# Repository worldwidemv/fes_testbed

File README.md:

# Testbed for Functional Electrical Stimulation (FES) Devices

## Abstract
The FES Testbed is a specialised data acquisition system for measurements of transcutaneous electrical stimulation setups. The galvanic isolated measurement system transfers the high-resolution data of every detected
stimulation pulse via USB to a PC or Laptop. The stimulation pulse can use one of the 3 included skin replacement
models or can be forwarded to standard electrodes, allowing to record a normal FES application. Modular
postprocessing MATLAB functions round up the FES Testbed. These functions handle the data conversion, pulse
detection, gathering of statistics, data management and data visualisation. A MATLAB GUI for efficient pulse
examination completes the FES Testbed.

<p>
<a href="./Documentation/Vienna_FESWS_2019_FES_Testbed__Paper.pdf">More Information ...</a>
</p>

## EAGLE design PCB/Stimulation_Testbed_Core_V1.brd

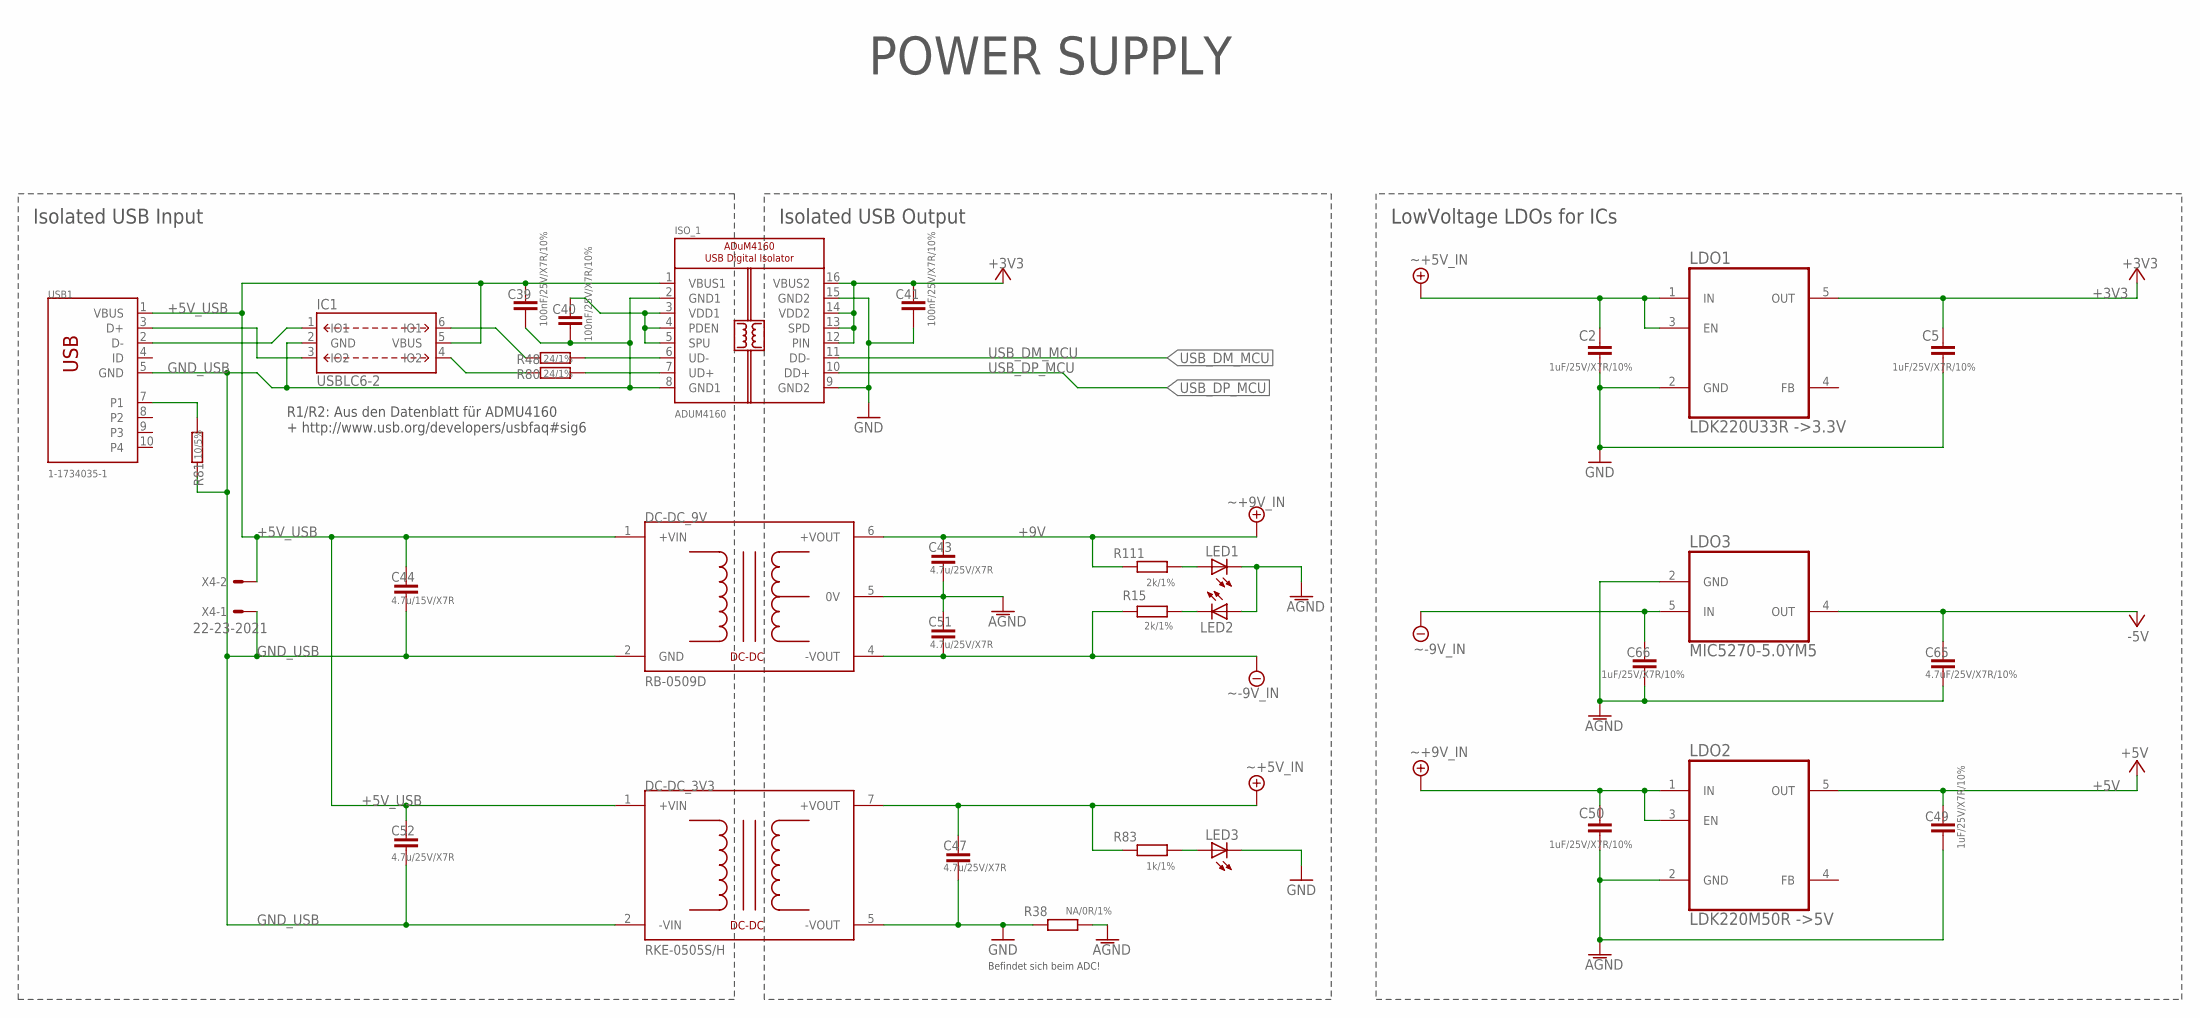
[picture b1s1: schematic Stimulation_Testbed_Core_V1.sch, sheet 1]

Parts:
C2, C5, C49, C50, C66: 1uF/25V/X7R/10%; C0603K
C39, C40, C41: 100nF/25V/X7R/10%; C0603K
C43, C47, C51, C52: 4.7u/25V/X7R; C0603
C44: 4.7u/15V/X7R; C0603
C65: 4.7uF/25V/X7R/10%; C0603K
DC-DC_3V3: RKE-0505S/H; MEJ2
DC-DC_9V: RB-0509D; NMH
IC1: USBLC6-2; SOT-23-6
ISO_1: ADUM4160; SOIC16WIDE
LDO1: LDK220U33R ->3.3V; SOT-23-5
LDO2: LDK220M50R ->5V; SOT-23-5
LDO3: MIC5270-5.0YM5; SOT-23-5
LED1, LED2, LED3: LEDCHIPLED_0603; CHIPLED_0603
R15, R111: 2k/1%; R0603
R38: NA/0R/1%; R0603
R48, R80: 24/1%; R0603
R81: 10/5%; R0603
R83: 1k/1%; R0603
USB1: 1-1734035-1; TE_1-1734035-1
X4: 22-23-2021

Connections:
+3V3: C5.1, C41.1, ISO_1.12 (PIN), ISO_1.13 (SPD), ISO_1.14 (VDD2), ISO_1.16 (VBUS2), LDO1.5 (OUT); also elsewhere on the board
+5V: C49.1, LDO2.5 (OUT); also elsewhere on the board
+5V_IN: C2.1, C47.1, DC-DC_3V3.7 (+VOUT), LDO1.1 (IN), LDO1.3 (EN), R83.1
+5V_USB: C39.1, C44.1, C52.1, DC-DC_3V3.1 (+VIN), DC-DC_9V.1 (+VIN), IC1.5 (VBUS), ISO_1.1 (VBUS1), USB1.1 (VBUS), X4.2
+9V: C43.1, C50.1, DC-DC_9V.6 (+VOUT), LDO2.1 (IN), LDO2.3 (EN), R111.1
-5V: C65.1, LDO3.4 (OUT); also elsewhere on the board
-9V: C51.2, C66.1, DC-DC_9V.4 (-VOUT), LDO3.5 (IN), R15.2
AGND: C43.2, C49.2, C50.2, C51.1, C65.2, C66.2, DC-DC_9V.5 (0V), LDO2.2 (GND), LDO3.2 (GND), LED1.C, LED2.A, R38.2; also elsewhere on the board
GND: C2.2, C5.2, C41.2, C47.2, DC-DC_3V3.5 (-VOUT), ISO_1.9 (GND2), ISO_1.15 (GND2), LDO1.2 (GND), LED3.C, R38.1; also elsewhere on the board
GND_USB: C39.2, C40.2, C44.2, C52.2, DC-DC_3V3.2 (-VIN), DC-DC_9V.2 (GND), IC1.2 (GND), ISO_1.2 (GND1), ISO_1.8 (GND1), R81.1, USB1.5 (GND), X4.1
unnamed: IC1.6 (IO1), R48.1
unnamed: C40.1, ISO_1.3 (VDD1), ISO_1.4 (PDEN), ISO_1.5 (SPU)
unnamed: ISO_1.6 (UD-), R48.2
unnamed: ISO_1.7 (UD+), R80.2
unnamed: R81.2, USB1.7 (P1)
unnamed: LED2.C, R15.1
unnamed: LED3.A, R83.2
unnamed: LED1.A, R111.2
unnamed: IC1.3 (IO2), USB1.3 (D+)
unnamed: IC1.1 (IO1), USB1.2 (D-)
unnamed: IC1.4 (IO2), R80.1
USB_DM_MCU: ISO_1.11 (DD-); also elsewhere on the board
USB_DP_MCU: ISO_1.10 (DD+); also elsewhere on the board

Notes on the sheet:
R1/R2: Aus den Datenblatt für ADMU4160 + http://www.usb.org/developers/usbfaq#sig6
Isolated USB Input
LowVoltage LDOs for ICs
Isolated USB Output
POWER SUPPLY
Befindet sich beim ADC!

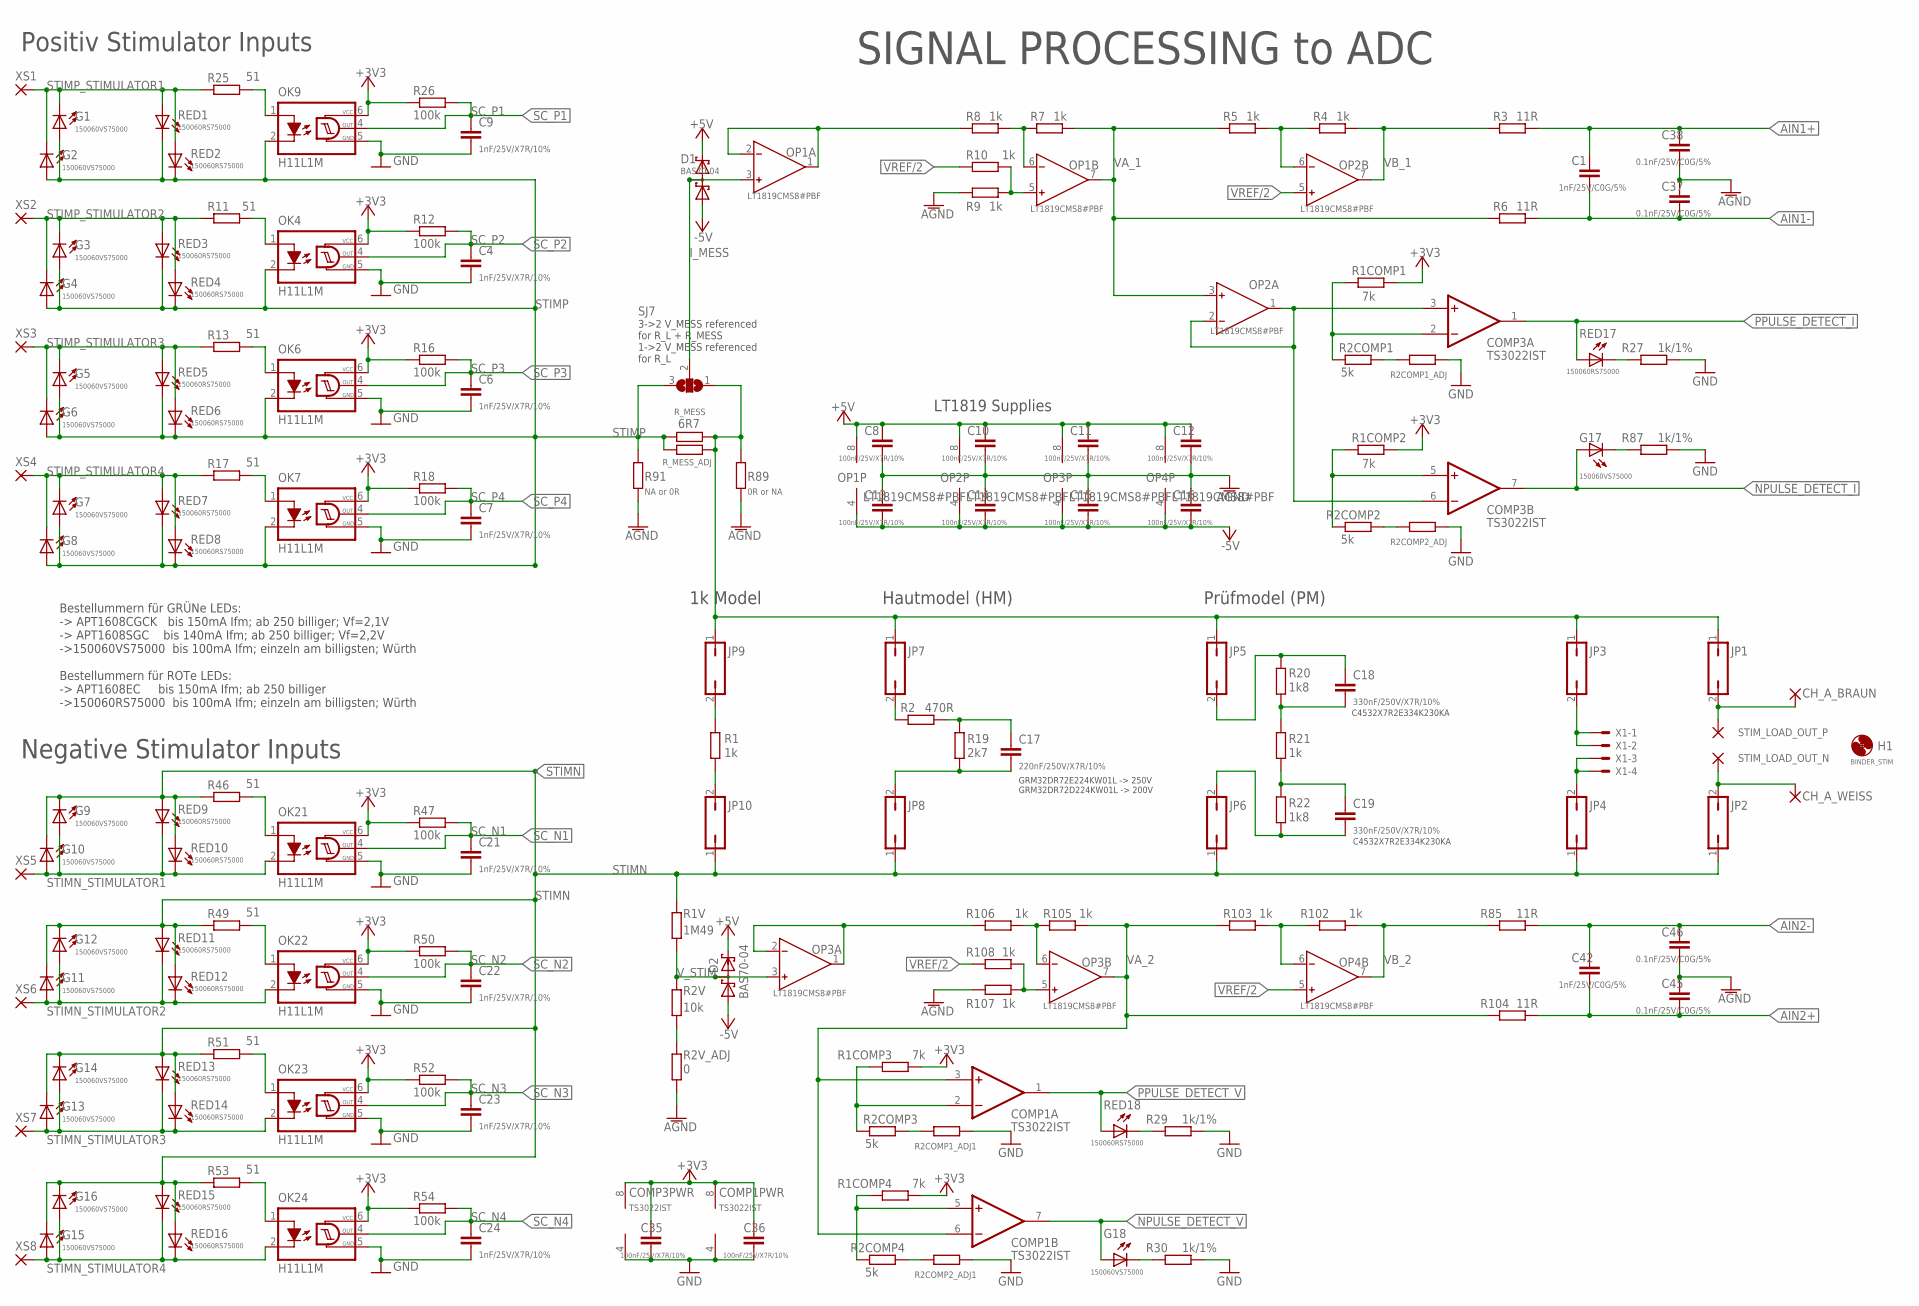
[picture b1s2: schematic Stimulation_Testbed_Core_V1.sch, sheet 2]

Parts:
C1, C42: 1nF/25V/C0G/5%; C0603K
C4, C6, C7, C9, C21, C22, C23, C24: 1nF/25V/X7R/10%; C0603
C8, C10, C11, C12, C13, C14, C15, C16, C35, C36: 100nF/25V/X7R/10%; C0603K
C17: 220nF/250V/X7R/10%; C1210
C18, C19: 330nF/250V/X7R/10%; C1812
C37, C38, C45, C46: 0.1nF/25V/C0G/5%; C0603K
CH_A_BRAUN: 1,6/0,8
CH_A_WEISS: 1,6/0,8
COMP1, COMP3: TS3022IST; MSOP8
D1, D2: BAS70-04; SOT23
G1, G2, G3, G4, G5, G6, G7, G8, G9, G10, G11, G12, G13, G14, G15, G16, G17, G18: 150060VS75000; CHIPLED_0603
H1: BINDER_STIM; 5,5-PAD
JP1, JP2, JP3, JP4, JP5, JP6, JP7, JP8, JP9, JP10: JP1Q; JP1
OK4, OK6, OK7, OK9, OK21, OK22, OK23, OK24: H11L1M; DIL06
OP1, OP2, OP3, OP4: LT1819CMS8#PBF; MSOP8
R1, R21: 1k; R1206
R1COMP1, R1COMP2, R1COMP3, R1COMP4: 7k; R0603
R1V: 1M49; R1206
R2: 470R; R1206
R2COMP1, R2COMP2, R2COMP3, R2COMP4: 5k; R0603
R2COMP1_ADJ, R2COMP1_ADJ1: R-EU_R0603; R0603
R2COMP2_ADJ, R2COMP2_ADJ1, R4, R5, R7, R8, R9, R10, R102, R103, R105, R106, R107, R108: 1k; R0603
R2V: 10k; R1206
R2V_ADJ: 0; R1206
R3, R6, R85, R104: 11R; R0603
R11, R13, R17, R25, R46, R49, R51, R53: 51; R0603
R12, R16, R18, R26, R47, R50, R52, R54: 100k; R0603
R19: 2k7; R1206
R20, R22: 1k8; R1206
R27, R29, R30, R87: 1k/1%; R0603
R89: 0R or NA; R0603
R91: NA or 0R; R0603
RED1, RED2, RED3, RED4, RED5, RED6, RED7, RED8, RED9, RED10, RED11, RED12, RED13, RED14, RED15, RED16, RED17, RED18: 150060RS75000; CHIP-LED0603
R_MESS: 6R7; R1206
R_MESS_ADJ: R-EU_R1206; R1206
SJ7: SJ2W; SJ_2
STIM_LOAD_OUT_N: 3,81/1,4
STIM_LOAD_OUT_P: 3,81/1,4
X1: 22-23-2041
XS1, XS2, XS3, XS4, XS5, XS6, XS7, XS8: WIREPAD3,81/1,4; 3,81/1,4

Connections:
2XVREF: OP3.1 (OUT), OP3.2 (IN-), R106.2
2XVREF1: OP1.1 (OUT), OP1.2 (IN-), R8.2
+3V3: C35.1, C36.1, COMP1.8 (V+), COMP3.8 (V+), OK4.6 (VCC), OK6.6 (VCC), OK7.6 (VCC), OK9.6 (VCC), OK21.6 (VCC), OK22.6 (VCC), OK23.6 (VCC), OK24.6 (VCC), R1COMP1.1, R1COMP2.1, R1COMP3.1, R1COMP4.1, R12.1, R16.1, R18.1, R26.1, R47.1, R50.1, R52.1, R54.1; also elsewhere on the board
+5V: C8.1, C10.1, C11.1, C12.1, D1.2 (C2), D2.2 (C2), OP1.8 (V+), OP2.8 (V+), OP3.8 (V+), OP4.8 (V+); also elsewhere on the board
-5V: C13.2, C14.2, C15.2, C16.2, D1.1 (A1), D2.1 (A1), OP1.4 (V-), OP2.4 (V-), OP3.4 (V-), OP4.4 (V-); also elsewhere on the board
AGND: C8.2, C10.2, C11.2, C12.2, C13.1, C14.1, C15.1, C16.1, C37.2, C38.1, C45.2, C46.1, R2V_ADJ.2, R9.2, R89.2, R91.2, R107.2; also elsewhere on the board
AIN1+: C1.2, C38.2, R3.1; also elsewhere on the board
AIN1-: C1.1, C37.1, R6.2; also elsewhere on the board
AIN2+: C42.1, C45.1, R104.2; also elsewhere on the board
AIN2-: C42.2, C46.2, R85.1; also elsewhere on the board
GND: C4.2, C6.2, C7.2, C9.2, C21.2, C22.2, C23.2, C24.2, C35.2, C36.2, COMP1.4 (V-), COMP3.4 (V-), OK4.5 (GND), OK6.5 (GND), OK7.5 (GND), OK9.5 (GND), OK21.5 (GND), OK22.5 (GND), OK23.5 (GND), OK24.5 (GND), R2COMP1_ADJ.1, R2COMP1_ADJ1.1, R2COMP2_ADJ.1, R2COMP2_ADJ1.1, R27.1, R29.1, R30.1, R87.1; also elsewhere on the board
I_MESS: D1.3 (C1A2), OP1.3 (IN+), SJ7.2
unnamed: OK4.1 (A), R11.1
unnamed: R2COMP2.2, R2COMP2_ADJ.2
unnamed: R29.2, RED18.C
unnamed: G18.C, R30.2
unnamed: COMP1.2 (-IN), R1COMP3.2, R2COMP3.1
unnamed: COMP1.5 (+IN), R1COMP4.2, R2COMP4.1
unnamed: G17.C, R87.2
unnamed: OP1.5 (IN+), R9.1, R10.1
unnamed: R2COMP1_ADJ1.2, R2COMP3.2
unnamed: R2COMP2_ADJ1.2, R2COMP4.2
unnamed: OK6.1 (A), R13.1
unnamed: OK7.1 (A), R17.1
unnamed: OK9.1 (A), R25.1
unnamed: OP1.6 (IN-), R7.2, R8.1
unnamed: OP2.6 (IN-), R4.2, R5.1
unnamed: COMP3.3 (+IN), COMP3.6 (-IN), OP2.1 (OUT), OP2.2 (IN-)
unnamed: OK21.1 (A), R46.1
unnamed: COMP3.2 (-IN), R1COMP1.2, R2COMP1.1
unnamed: CH_A_WEISS.1, JP2.2, STIM_LOAD_OUT_N.1
unnamed: OK22.1 (A), R49.1
unnamed: OK23.1 (A), R51.1
unnamed: OK24.1 (A), R53.1
unnamed: R2V.1, R2V_ADJ.1
unnamed: OP3.5 (IN+), R107.1, R108.1
unnamed: CH_A_BRAUN.1, JP1.2, STIM_LOAD_OUT_P.1
unnamed: JP3.2, X1.1, X1.2
unnamed: JP9.2, R1.1
unnamed: JP4.2, X1.3, X1.4
unnamed: JP10.2, R1.2
unnamed: JP7.2, R2.2
unnamed: OP3.6 (IN-), R105.2, R106.1
unnamed: C17.1, JP8.2, R19.2
unnamed: C19.2, R21.2, R22.1
unnamed: C19.1, JP6.2, R22.2
unnamed: C18.2, JP5.2, R20.1
unnamed: C18.1, R20.2, R21.1
unnamed: OP4.6 (IN-), R102.2, R103.1
unnamed: C17.2, R2.1, R19.1
unnamed: R27.2, RED17.C
unnamed: COMP3.5 (+IN), R1COMP2.2, R2COMP2.1
unnamed: R2COMP1.2, R2COMP1_ADJ.2
NPULSE_DETECT_I: COMP3.7 (OUT), G17.A; also elsewhere on the board
NPULSE_DETECT_V: COMP1.7 (OUT), G18.A; also elsewhere on the board
PPULSE_DETECT_I: COMP3.1 (OUT), RED17.A; also elsewhere on the board
PPULSE_DETECT_V: COMP1.1 (OUT), RED18.A; also elsewhere on the board
SC_N1: C21.1, OK21.4 (OUT), R47.2; also elsewhere on the board
SC_N2: C22.1, OK22.4 (OUT), R50.2; also elsewhere on the board
SC_N3: C23.1, OK23.4 (OUT), R52.2; also elsewhere on the board
SC_N4: C24.1, OK24.4 (OUT), R54.2; also elsewhere on the board
SC_P1: C9.1, OK9.4 (OUT), R26.2; also elsewhere on the board
SC_P2: C4.1, OK4.4 (OUT), R12.2; also elsewhere on the board
SC_P3: C6.1, OK6.4 (OUT), R16.2; also elsewhere on the board
SC_P4: C7.1, OK7.4 (OUT), R18.2; also elsewhere on the board
STIMN: G9.C, G10.C, G11.C, G12.C, G13.C, G14.C, G15.C, G16.C, JP2.1, JP4.1, JP6.1, JP8.1, JP10.1, R1V.2, R46.2, R49.2, R51.2, R53.2, RED9.A, RED10.A, RED11.A, RED12.A, RED13.A, RED14.A, RED15.A, RED16.A; also elsewhere on the board
STIMN_STIMULATOR1: G9.A, G10.A, OK21.2 (C), RED9.C, RED10.C, XS5.1
STIMN_STIMULATOR2: G11.A, G12.A, OK22.2 (C), RED11.C, RED12.C, XS6.1
STIMN_STIMULATOR3: G13.A, G14.A, OK23.2 (C), RED13.C, RED14.C, XS7.1
STIMN_STIMULATOR4: G15.A, G16.A, OK24.2 (C), RED15.C, RED16.C, XS8.1
STIMP: G1.A, G2.A, G3.A, G4.A, G5.A, G6.A, G7.A, G8.A, OK4.2 (C), OK6.2 (C), OK7.2 (C), OK9.2 (C), R91.1, RED1.C, RED2.C, RED3.C, RED4.C, RED5.C, RED6.C, RED7.C, RED8.C, R_MESS.2, R_MESS_ADJ.1, SJ7.3; also elsewhere on the board
STIMP_MODEL: JP1.1, JP3.1, JP5.1, JP7.1, JP9.1, R89.1, R_MESS.1, R_MESS_ADJ.2, SJ7.1
STIMP_STIMULATOR1: G1.C, G2.C, R25.2, RED1.A, RED2.A, XS1.1
STIMP_STIMULATOR2: G3.C, G4.C, R11.2, RED3.A, RED4.A, XS2.1
STIMP_STIMULATOR3: G5.C, G6.C, R13.2, RED5.A, RED6.A, XS3.1
STIMP_STIMULATOR4: G7.C, G8.C, R17.2, RED7.A, RED8.A, XS4.1
VA_1: OP1.7 (OUT), OP2.3 (IN+), R5.2, R6.1, R7.1
VA_2: COMP1.3 (+IN), COMP1.6 (-IN), OP3.7 (OUT), R103.2, R104.1, R105.1
VB_1: OP2.7 (OUT), R3.2, R4.1
VB_2: OP4.7 (OUT), R85.2, R102.1
VREF/2: OP2.5 (IN+), OP4.5 (IN+), R10.2, R108.2; also elsewhere on the board
V_STIM: D2.3 (C1A2), OP3.3 (IN+), R1V.1, R2V.2

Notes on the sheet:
LT1819 Supplies
1k Model
Hautmodel (HM)
Prüfmodel (PM)
SIGNAL PROCESSING to ADC
3->2 V_MESS referenced for R_L + R_MESS 1->2 V_MESS referenced for R_L
Positiv Stimulator Inputs
Negative Stimulator Inputs
C4532X7R2E334K230KA
GRM32DR72E224KW01L -> 250V GRM32DR72D224KW01L -> 200V
Bestellummern für GRÜNe LEDs: -> APT1608CGCK bis 150mA Ifm; ab 250 billiger; Vf=2,1V -> APT1608SGC bis 140mA Ifm; ab 250 billiger; Vf=2,2V ->150060VS75000 bis 100mA Ifm; einzeln am billigsten; Würth Bestellummern für ROTe LEDs: -> APT1608EC bis 150mA Ifm; ab 250 billiger ->150060RS75000 bis 100mA I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

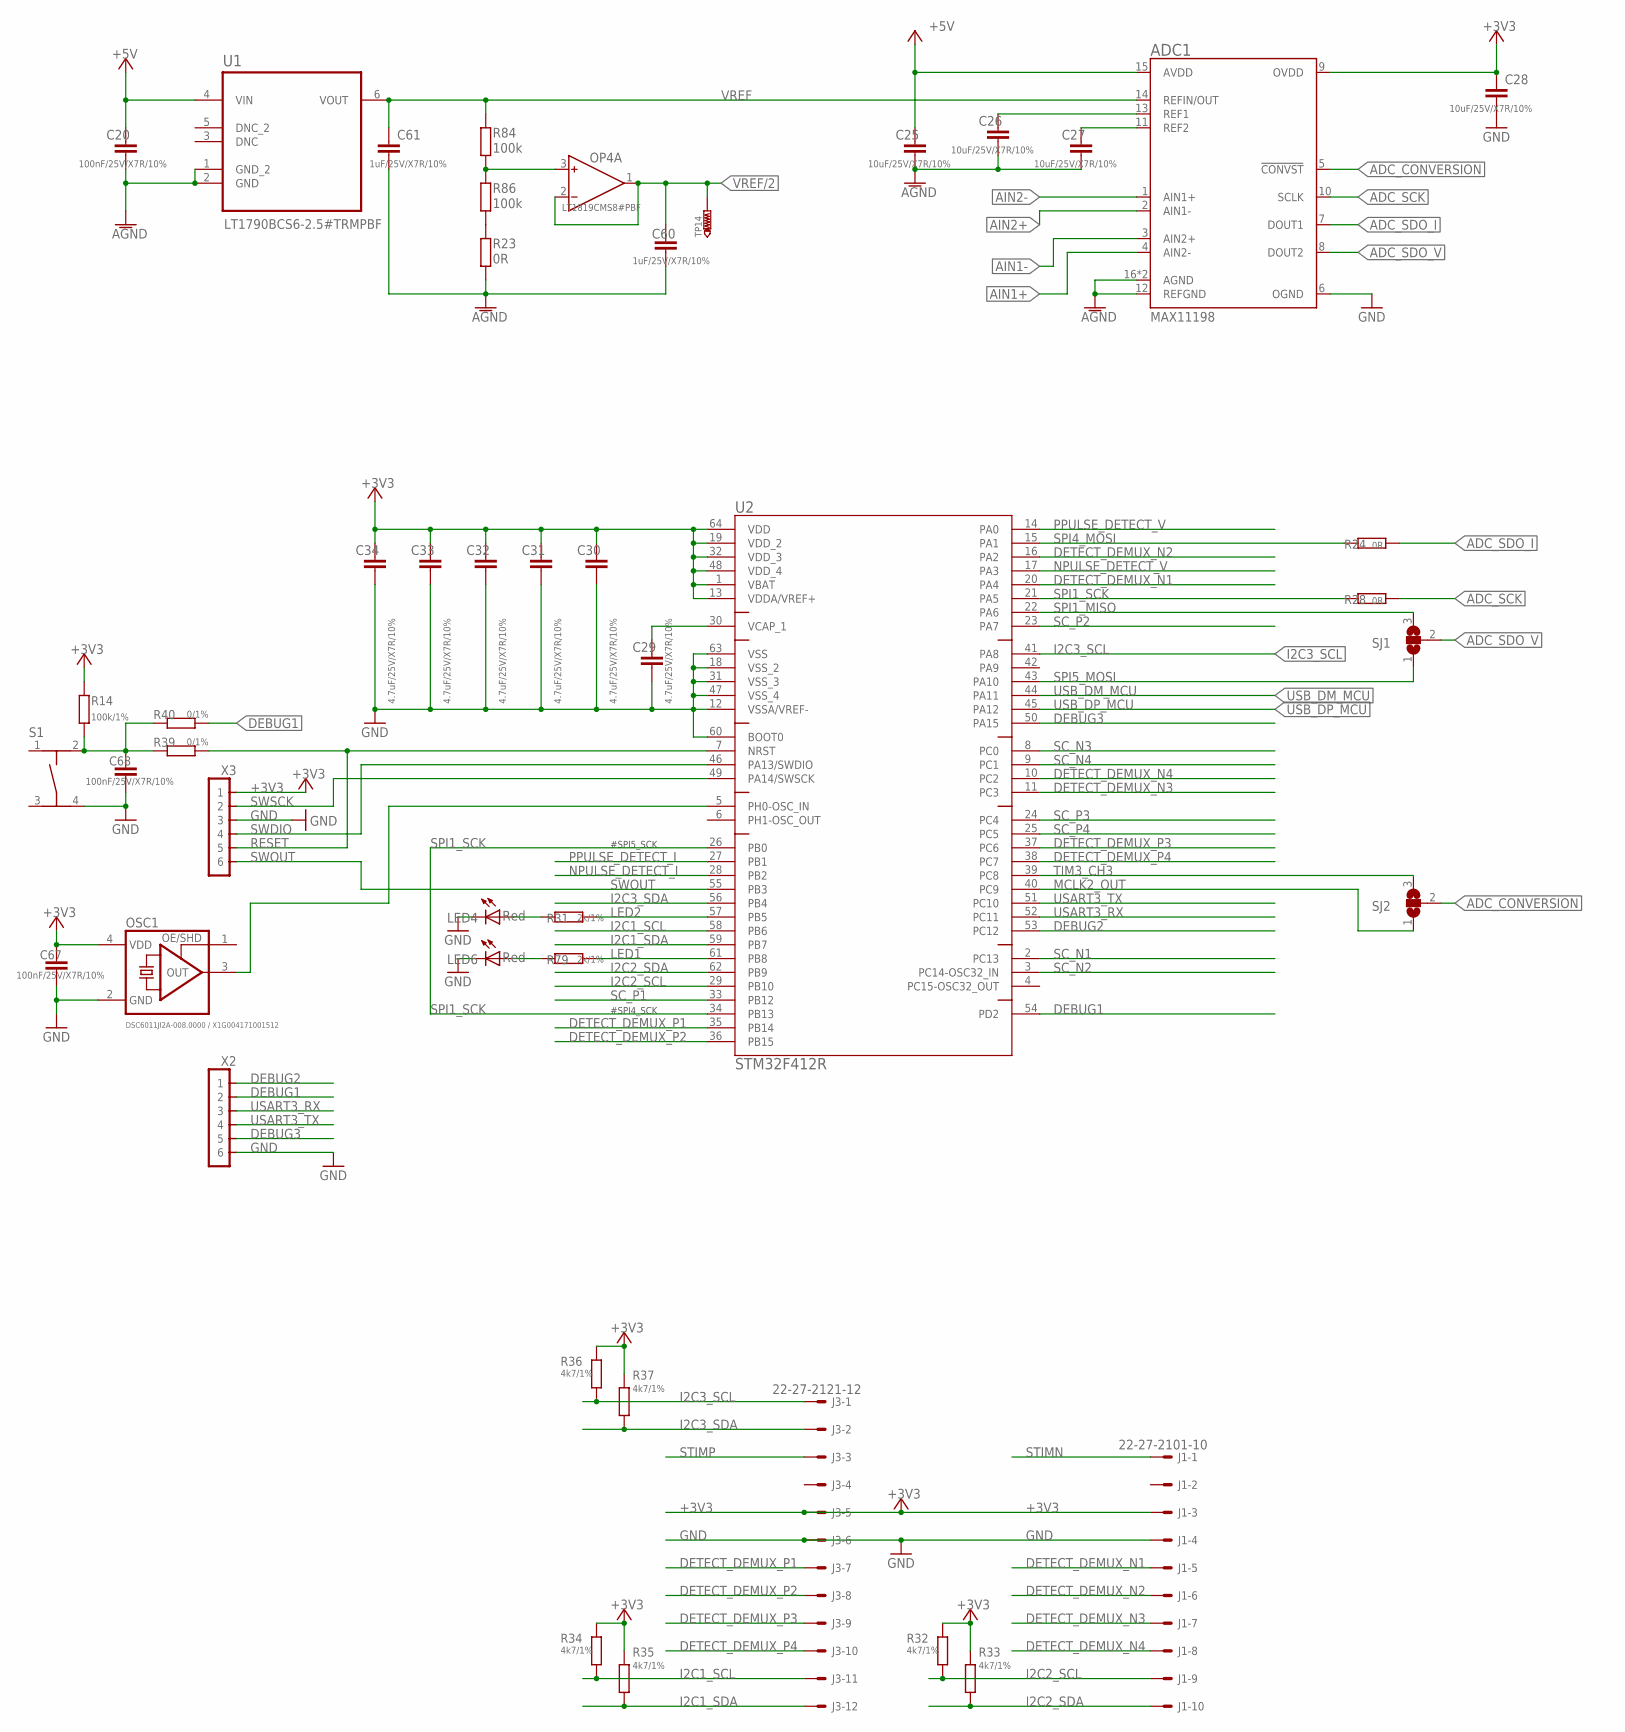
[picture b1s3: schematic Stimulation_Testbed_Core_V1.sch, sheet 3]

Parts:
ADC1: MAX11198; T1623CN+1
C20, C67, C68: 100nF/25V/X7R/10%; C0603K
C25, C26, C27, C28: 10uF/25V/X7R/10%; C0603K
C29, C30, C31, C32, C33, C34: 4.7uF/25V/X7R/10%; C0603K
C60, C61: 1uF/25V/X7R/10%; C0603K
J1: 22-27-2101-10; 6410-10
J3: 22-27-2121-12; 6410-12
LED4, LED6: Red; CHIPLED_0603
OP4: LT1819CMS8#PBF; MSOP8
OSC1: DSC6011JI2A-008.0000 / X1G004171001512; OSC_2.5X2
R14: 100k/1%; R0603
R23, R24, R28: 0R; R0603
R31, R79: 2k/1%; R0603
R32, R33, R34, R35, R36, R37: 4k7/1%; R0603
R39, R40: 0/1%; R0603
R84, R86: 100k; R0603
S1: TASTERSMD; TAST_SMD
SJ1, SJ2: SJ2W; SJ_2
TP14: TESTPOINT_TH; TP1-09
U1: LT1790BCS6-2.5#TRMPBF; SOT95P280X100-6N
U2: STM32F412R; LQFP64-10X10MM
X2, X3: PINHD-1X66X1.27; 1.27_1X06_S

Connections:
+3V3: ADC1.9 (OVDD), C28.1, C30.1, C31.1, C32.1, C33.1, C34.1, C67.1, J1.3, J3.5, OSC1.4 (VDD), R14.2, R32.1, R33.1, R34.1, R35.1, R36.1, R37.1, U2.1 (VBAT), U2.13 (VDDA/VREF+), U2.19 (VDD_2), U2.32 (VDD_3), U2.48 (VDD_4), U2.64 (VDD), X3.P1 (1); also elsewhere on the board
+5V: ADC1.15 (AVDD), C20.1, C25.1, U1.4 (VIN); also elsewhere on the board
ADC_CONVERSION: ADC1.5 (!CONVST!), SJ2.2
ADC_SCK: ADC1.10 (SCLK), R28.2
ADC_SDO_I: ADC1.7 (DOUT1), R24.2
ADC_SDO_V: ADC1.8 (DOUT2), SJ1.2
AGND: ADC1.12 (REFGND), ADC1.16 (AGND), ADC1.EXP (AGND), C20.2, C25.2, C26.2, C27.2, C60.2, C61.2, R23.2, U1.1 (GND_2), U1.2 (GND); also elsewhere on the board
AIN1+: ADC1.4 (AIN2-); also elsewhere on the board
AIN1-: ADC1.3 (AIN2+); also elsewhere on the board
AIN2+: ADC1.2 (AIN1-); also elsewhere on the board
AIN2-: ADC1.1 (AIN1+); also elsewhere on the board
DEBUG1: R40.1, U2.54 (PD2), X2.P2 (2)
DEBUG2: U2.53 (PC12), X2.P1 (1)
DEBUG3: U2.50 (PA15), X2.P5 (5)
DETECT_DEMUX_N1: J1.5, U2.20 (PA4)
DETECT_DEMUX_N2: J1.6, U2.16 (PA2)
DETECT_DEMUX_N3: J1.7, U2.11 (PC3)
DETECT_DEMUX_N4: J1.8, U2.10 (PC2)
DETECT_DEMUX_P1: J3.7, U2.35 (PB14)
DETECT_DEMUX_P2: J3.8, U2.36 (PB15)
DETECT_DEMUX_P3: J3.9, U2.37 (PC6)
DETECT_DEMUX_P4: J3.10, U2.38 (PC7)
GND: ADC1.6 (OGND), C28.2, C29.2, C30.2, C31.2, C32.2, C33.2, C34.2, C67.2, C68.2, J1.4, J3.6, LED4.C, LED6.C, OSC1.2 (GND), S1.4, U2.12 (VSSA/VREF-), U2.18 (VSS_2), U2.31 (VSS_3), U2.47 (VSS_4), U2.60 (BOOT0), U2.63 (VSS), X2.P6 (6), X3.P3 (3); also elsewhere on the board
I2C1_SCL: J3.11, R34.2, U2.58 (PB6)
I2C1_SDA: J3.12, R35.2, U2.59 (PB7)
I2C2_SCL: J1.9, R32.2, U2.29 (PB10)
I2C2_SDA: J1.10, R33.2, U2.62 (PB9)
I2C3_SCL: J3.1, R36.2, U2.41 (PA8)
I2C3_SDA: J3.2, R37.2, U2.56 (PB4)
LED1: R79.1, U2.61 (PB8)
LED2: R31.1, U2.57 (PB5)
MCLK2_OUT: SJ2.1, U2.40 (PC9)
unnamed: LED4.A, R31.2
unnamed: C29.1, U2.30 (VCAP_1)
unnamed: R23.1, R86.1
unnamed: C68.1, R14.1, R39.2, R40.2, S1.2
unnamed: ADC1.11 (REF2), C27.1
unnamed: ADC1.13 (REF1), C26.1
unnamed: OP4.3 (IN+), R84.2, R86.2
unnamed: OSC1.3 (OUT), U2.5 (PH0-OSC_IN)
unnamed: LED6.A, R79.2
NPULSE_DETECT_I: U2.28 (PB2); also elsewhere on the board
NPULSE_DETECT_V: U2.17 (PA3); also elsewhere on the board
PPULSE_DETECT_I: U2.27 (PB1); also elsewhere on the board
PPULSE_DETECT_V: U2.14 (PA0); also elsewhere on the board
RESET: R39.1, U2.7 (NRST), X3.P5 (5)
SC_N1: U2.2 (PC13); also elsewhere on the board
SC_N2: U2.3 (PC14-OSC32_IN); also elsewhere on the board
SC_N3: U2.8 (PC0); also elsewhere on the board
SC_N4: U2.9 (PC1); also elsewhere on the board
SC_P1: U2.33 (PB12); also elsewhere on the board
SC_P2: U2.23 (PA7); also elsewhere on the board
SC_P3: U2.24 (PC4); also elsewhere on the board
SC_P4: U2.25 (PC5); also elsewhere on the board
SPI1_MISO: SJ1.3, U2.22 (PA6)
SPI1_SCK: R28.1, U2.21 (PA5), U2.26 (PB0), U2.34 (PB13)
SPI4_MOSI: R24.1, U2.15 (PA1)
SPI5_MOSI: SJ1.1, U2.43 (PA10)
STIMN: J1.1; also elsewhere on the board
STIMP: J3.3; also elsewhere on the board
SWDIO: U2.46 (PA13/SWDIO), X3.P4 (4)
SWOUT: U2.55 (PB3), X3.P6 (6)
SWSCK: U2.49 (PA14/SWSCK), X3.P2 (2)
TIM3_CH3: SJ2.3, U2.39 (PC8)
USART3_RX: U2.52 (PC11), X2.P3 (3)
USART3_TX: U2.51 (PC10), X2.P4 (4)
USB_DM_MCU: U2.44 (PA11); also elsewhere on the board
USB_DP_MCU: U2.45 (PA12); also elsewhere on the board
VREF: ADC1.14 (REFIN/OUT), C61.1, R84.1, U1.6 (VOUT)
VREF/2: C60.1, OP4.1 (OUT), OP4.2 (IN-), TP14.TP; also elsewhere on the board

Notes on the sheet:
#SPI5_SCK
#SPI4_SCK

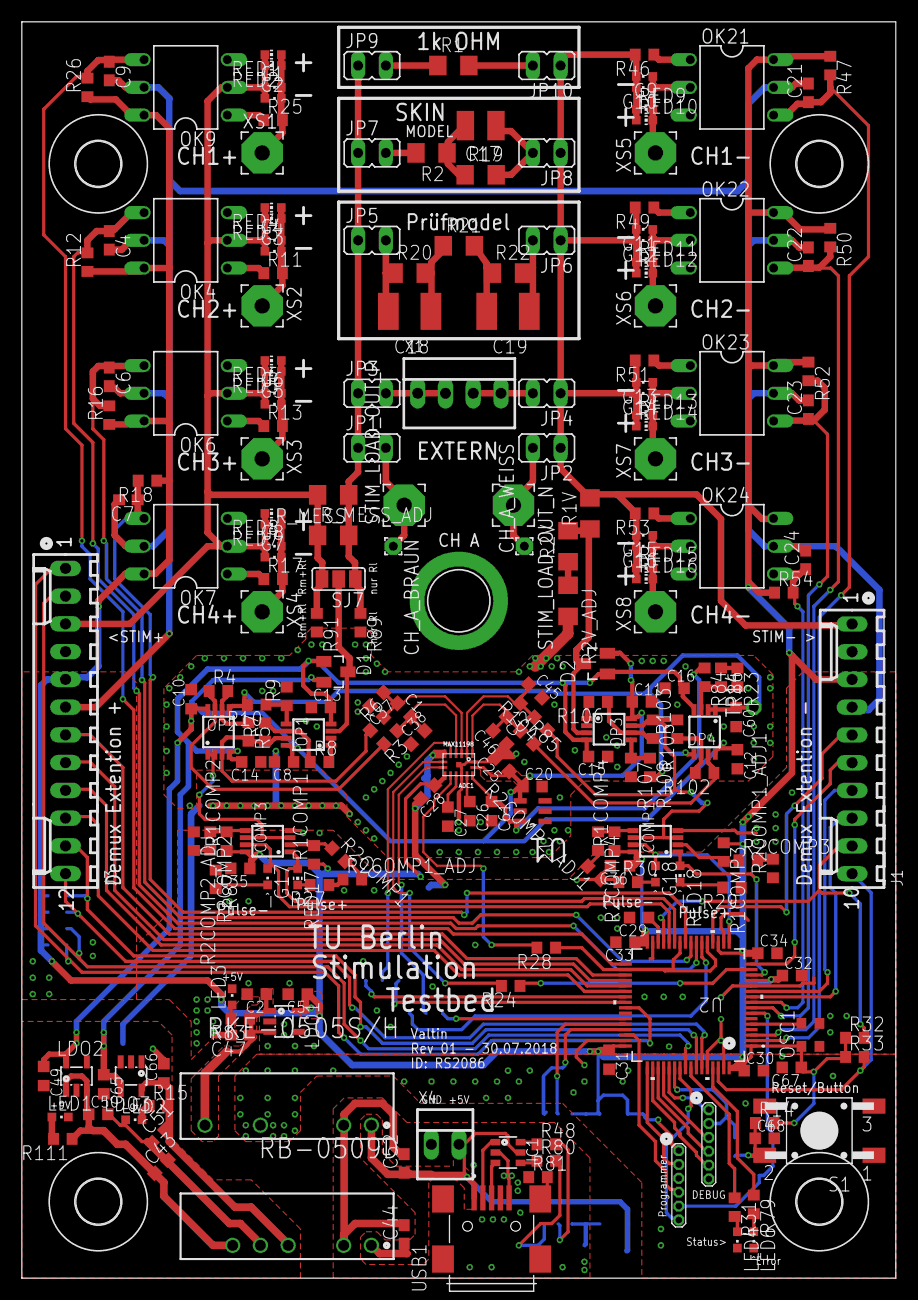
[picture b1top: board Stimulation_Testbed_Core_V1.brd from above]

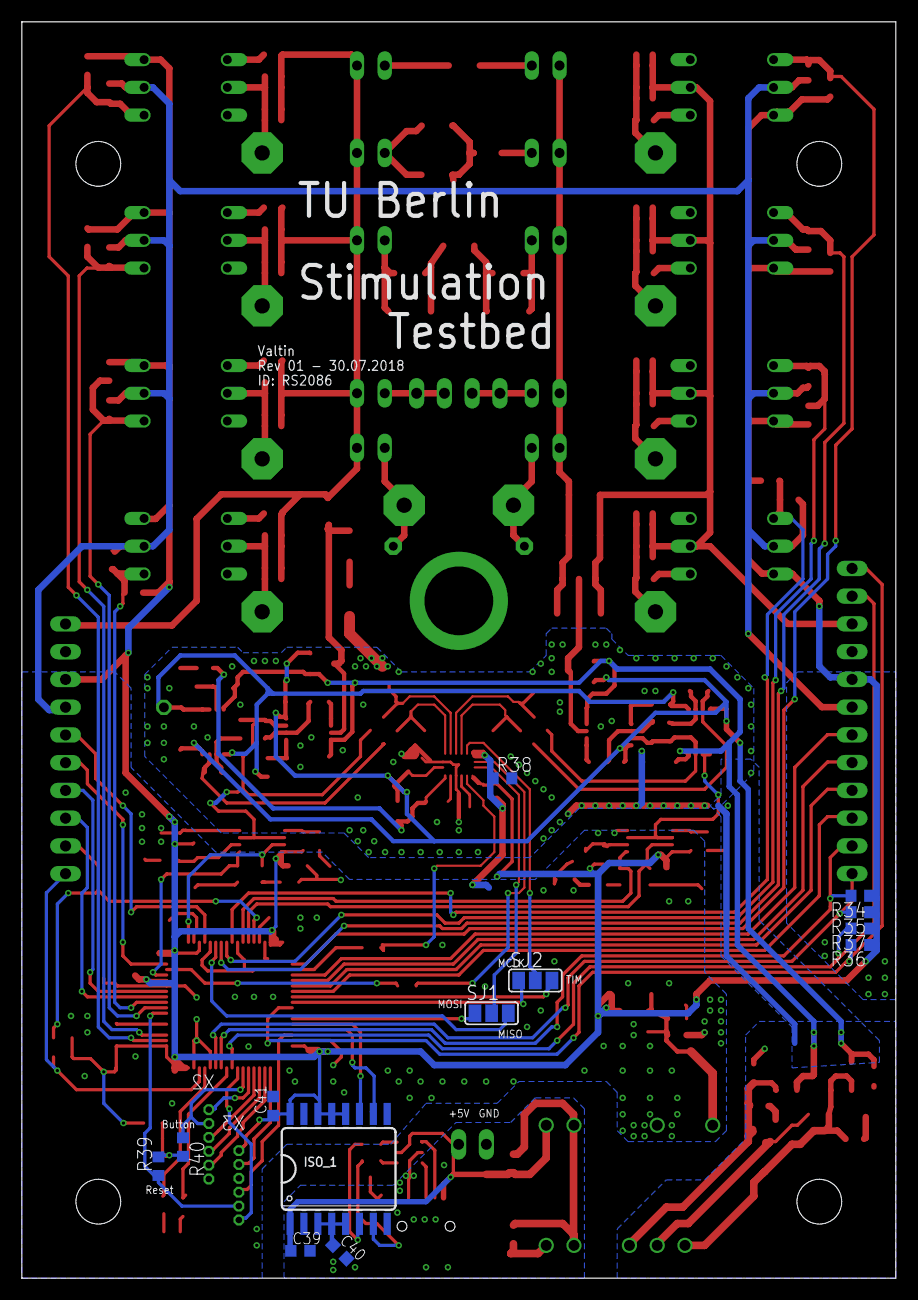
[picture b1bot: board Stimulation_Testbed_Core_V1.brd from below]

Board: 2 copper layers, 80.0 x 115.0 mm, 247 parts (13 on the bottom side), 145 nets.

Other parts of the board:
U$1, U$2, U$3, U$4: 4,1

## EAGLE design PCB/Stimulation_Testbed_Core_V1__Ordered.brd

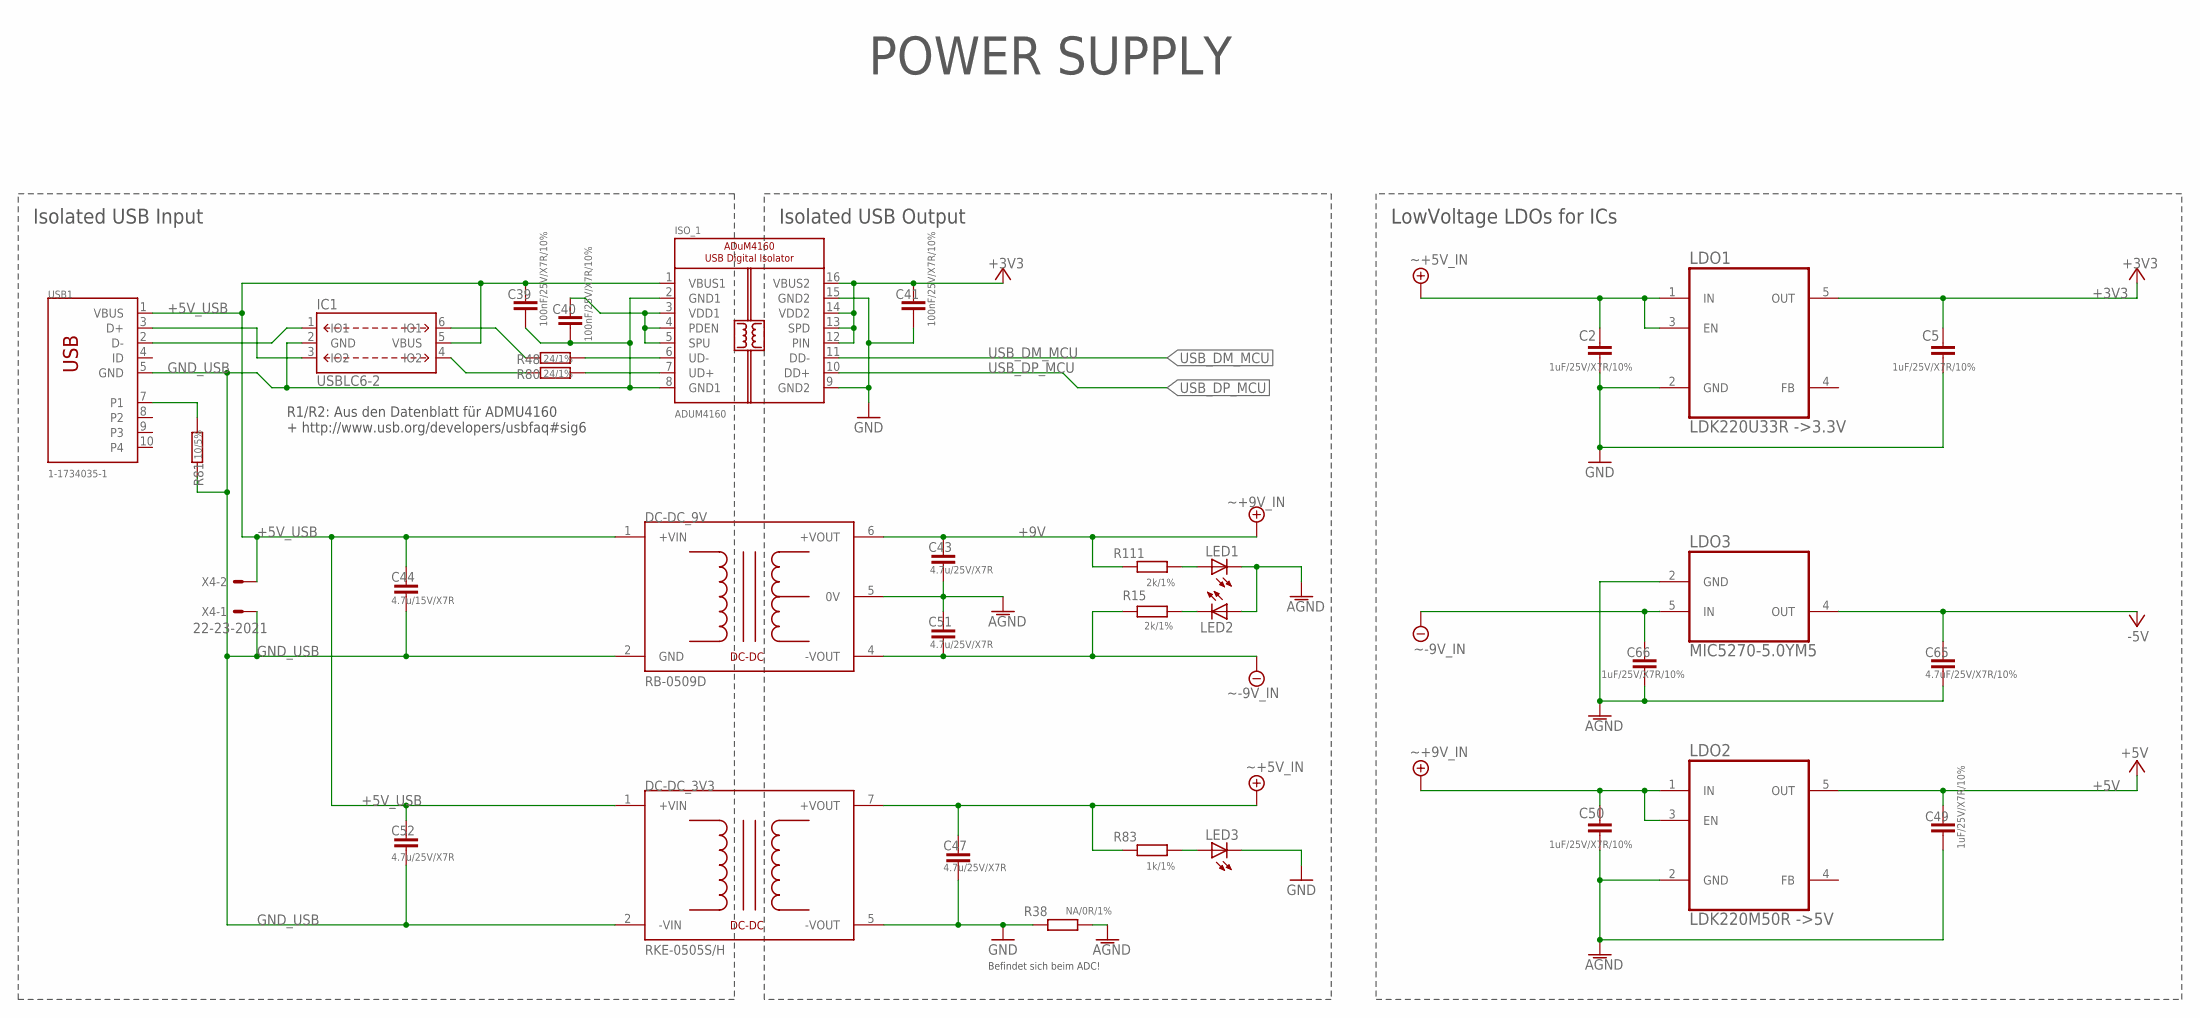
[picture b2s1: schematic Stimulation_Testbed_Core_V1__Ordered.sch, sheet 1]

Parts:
C2, C5, C49, C50, C66: 1uF/25V/X7R/10%; C0603K
C39, C40, C41: 100nF/25V/X7R/10%; C0603K
C43, C47, C51, C52: 4.7u/25V/X7R; C0603
C44: 4.7u/15V/X7R; C0603
C65: 4.7uF/25V/X7R/10%; C0603K
DC-DC_3V3: RKE-0505S/H; MEJ2
DC-DC_9V: RB-0509D; NMH
IC1: USBLC6-2; SOT-23-6
ISO_1: ADUM4160; SOIC16WIDE
LDO1: LDK220U33R ->3.3V; SOT-23-5
LDO2: LDK220M50R ->5V; SOT-23-5
LDO3: MIC5270-5.0YM5; SOT-23-5
LED1, LED2, LED3: LEDCHIPLED_0603; CHIPLED_0603
R15, R111: 2k/1%; R0603
R38: NA/0R/1%; R0603
R48, R80: 24/1%; R0603
R81: 10/5%; R0603
R83: 1k/1%; R0603
USB1: 1-1734035-1; TE_1-1734035-1
X4: 22-23-2021

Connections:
+3V3: C5.1, C41.1, ISO_1.12 (PIN), ISO_1.13 (SPD), ISO_1.14 (VDD2), ISO_1.16 (VBUS2), LDO1.5 (OUT); also elsewhere on the board
+5V: C49.1, LDO2.5 (OUT); also elsewhere on the board
+5V_IN: C2.1, C47.1, DC-DC_3V3.7 (+VOUT), LDO1.1 (IN), LDO1.3 (EN), R83.1
+5V_USB: C39.1, C44.1, C52.1, DC-DC_3V3.1 (+VIN), DC-DC_9V.1 (+VIN), IC1.5 (VBUS), ISO_1.1 (VBUS1), USB1.1 (VBUS), X4.2
+9V: C43.1, C50.1, DC-DC_9V.6 (+VOUT), LDO2.1 (IN), LDO2.3 (EN), R111.1
-5V: C65.1, LDO3.4 (OUT); also elsewhere on the board
-9V: C51.2, C66.1, DC-DC_9V.4 (-VOUT), LDO3.5 (IN), R15.2
AGND: C43.2, C49.2, C50.2, C51.1, C65.2, C66.2, DC-DC_9V.5 (0V), LDO2.2 (GND), LDO3.2 (GND), LED1.C, LED2.A, R38.2; also elsewhere on the board
GND: C2.2, C5.2, C41.2, C47.2, DC-DC_3V3.5 (-VOUT), ISO_1.9 (GND2), ISO_1.15 (GND2), LDO1.2 (GND), LED3.C, R38.1; also elsewhere on the board
GND_USB: C39.2, C40.2, C44.2, C52.2, DC-DC_3V3.2 (-VIN), DC-DC_9V.2 (GND), IC1.2 (GND), ISO_1.2 (GND1), ISO_1.8 (GND1), R81.1, USB1.5 (GND), X4.1
unnamed: IC1.6 (IO1), R48.1
unnamed: C40.1, ISO_1.3 (VDD1), ISO_1.4 (PDEN), ISO_1.5 (SPU)
unnamed: ISO_1.6 (UD-), R48.2
unnamed: ISO_1.7 (UD+), R80.2
unnamed: R81.2, USB1.7 (P1)
unnamed: LED2.C, R15.1
unnamed: LED3.A, R83.2
unnamed: LED1.A, R111.2
unnamed: IC1.3 (IO2), USB1.3 (D+)
unnamed: IC1.1 (IO1), USB1.2 (D-)
unnamed: IC1.4 (IO2), R80.1
USB_DM_MCU: ISO_1.11 (DD-); also elsewhere on the board
USB_DP_MCU: ISO_1.10 (DD+); also elsewhere on the board

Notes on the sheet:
R1/R2: Aus den Datenblatt für ADMU4160 + http://www.usb.org/developers/usbfaq#sig6
Isolated USB Input
LowVoltage LDOs for ICs
Isolated USB Output
POWER SUPPLY
Befindet sich beim ADC!

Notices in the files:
parts and their libraries:
Board-to-Board: Copyright: Würth Elektronik
